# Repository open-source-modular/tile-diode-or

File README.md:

# diode-or

An unpowered OR gate built from diodes. 1 input and 3 outputs.

Files are in KiCad 6 format.

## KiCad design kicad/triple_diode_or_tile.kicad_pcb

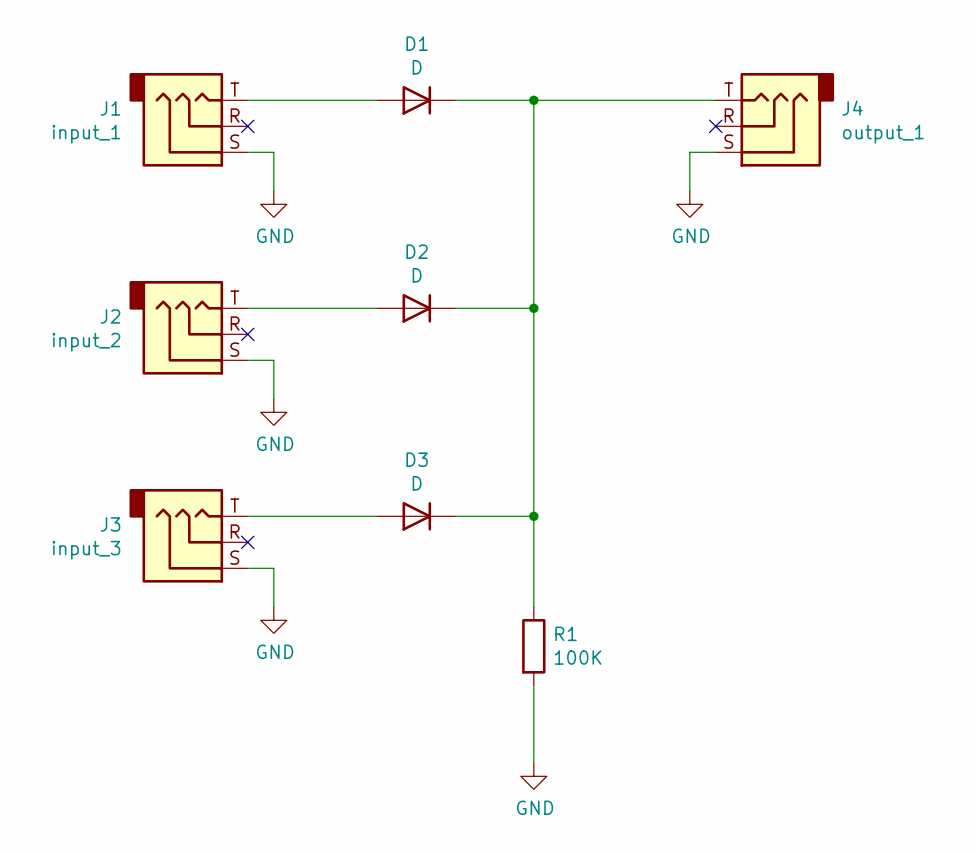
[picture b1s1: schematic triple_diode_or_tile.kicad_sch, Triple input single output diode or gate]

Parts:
D1, D2, D3: D; D_1206_3216Metric_Pad1.42x1.75mm_HandSolder
J1: input_1; PJ392-3.5mm-jack-vertical-SRT
J2: input_2; PJ392-3.5mm-jack-vertical-SRT
J3: input_3; PJ392-3.5mm-jack-vertical-SRT
J4: output_1; PJ392-3.5mm-jack-vertical-SRT
R1: 100K; R_1206_3216Metric_Pad1.30x1.75mm_HandSolder

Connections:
GND: J1.S, J2.S, J3.S, J4.S, R1.2
unnamed: D1.1 (K), D2.1 (K), D3.1 (K), J4.T, R1.1
unnamed: D1.2 (A), J1.T
unnamed: D2.2 (A), J2.T
unnamed: D3.2 (A), J3.T

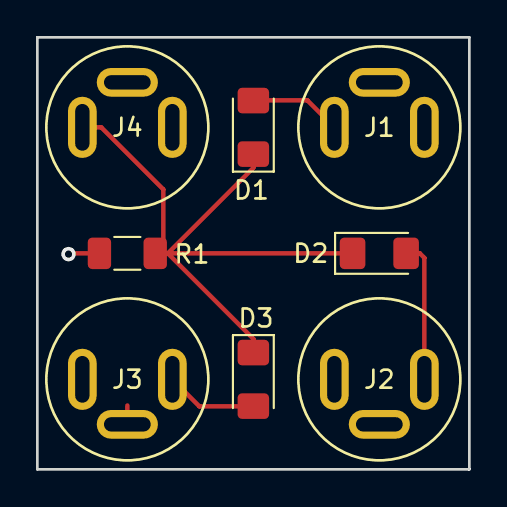
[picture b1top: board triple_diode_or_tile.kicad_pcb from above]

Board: 2 copper layers, 24.0 x 24.0 mm, 8 parts (0 on the bottom side), 5 nets.

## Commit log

2019-02-21 Changed library path
2022-10-24 Move kicad files to won subdir
2022-10-24 Added osm/footprints as submodule
2022-10-24 Converted to kicad 6
2022-10-24 Added renders of PCB
2022-10-24 Updated gitignore
2022-10-24 Minor updates as version 0.2. Added gerbers.
2022-10-24 Minor changes to readme
2022-10-24 Deleted unused kicad 5 files
